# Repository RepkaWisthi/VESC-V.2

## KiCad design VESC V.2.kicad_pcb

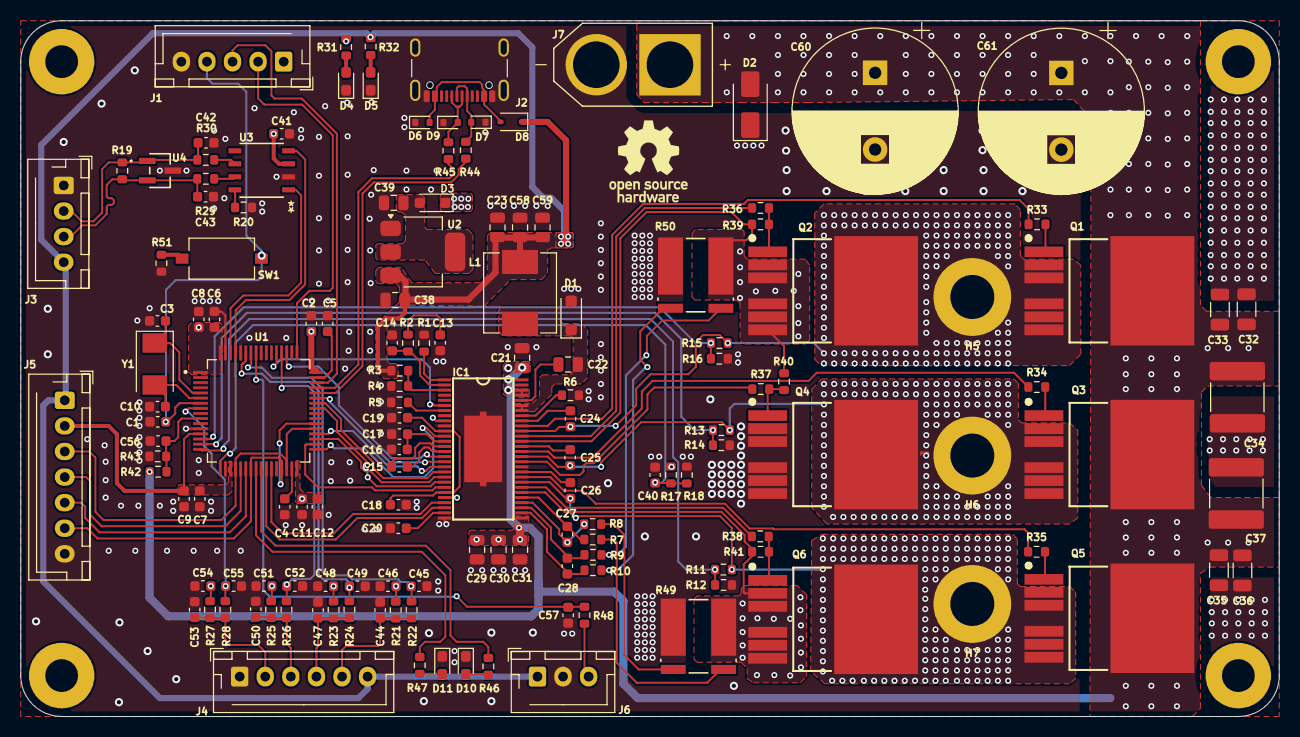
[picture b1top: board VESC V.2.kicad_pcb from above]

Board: 4 copper layers, 123.0 x 68.0 mm, 151 parts (0 on the bottom side), 102 nets.

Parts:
C1, C46, C48, C51, C54, C56, C57: 100nF; C_0603_1608Metric
C2, C4, C5, C6, C7, C8, C9, C11, C12, C16, C17, C18, C19, C20, C40, C41: 2.2uF; C_0603_1608Metric
C3, C10: 15pF; C_0603_1608Metric
C13: 6.8nF; C_0603_1608Metric
C14: 120pF; C_0603_1608Metric
C15: 22nF; C_0603_1608Metric
C21: 10uF/100V; C_0805_2012Metric
C22: 100nF; C_0805_2012Metric
C23, C38, C58, C59: 10uF; C_0805_2012Metric
C24, C25, C26: 220nF; C_0603_1608Metric
C27, C28: 2.2nF; C_0603_1608Metric
C29, C30, C31: 10uF/50V; C_0805_2012Metric
C32, C33, C35, C36: 10uF/50V; C_1206_3216Metric
C34, C37: 15uF/100V; C_2220_5750Metric
C39: 22uF; C_0805_2012Metric
C42, C43: 51pF; C_0603_1608Metric
C44, C45, C47, C49, C50, C52, C53, C55: 4.7nF; C_0603_1608Metric
C60, C61: 820uF/80V; CP_Radial_D16.0mm_P7.50mm
D1: PMEG6020; D_SOD-123F
D2: SMAJ60A; D_SMA
D3: BAT60A; D_SOD-323_HandSoldering
D4, D11: GREEN; LED_0603_1608Metric_Pad1.05x0.95mm_HandSolder
D5: RED; LED_0603_1608Metric_Pad1.05x0.95mm_HandSolder
D6, D7, D9: LESD5D5.0CT1G; D_SOD-523
D8: BAT760-7; D_SOD-323
D10: BLUE; LED_0603_1608Metric_Pad1.05x0.95mm_HandSolder
H1, H2, H3, H4: MountingHole_Pad; MountingHole_3.2mm_M3_Pad
H5, H6, H7: MountingHole_Pad; MountingHole_4.3mm_M4_ISO7380_Pad
IC1: DRV8302; TSSOP-56_3
J1: Conn_01x05_Socket; JST_XH_B5B-XH-AM_1x05_P2.50mm_Vertical
J2: USB_C_Receptacle_USB2.0_16P; USB_C_Receptacle_GCT_USB4105-xx-A_16P_TopMnt_Horizontal
J3: CAN BUS; JST_XH_B4B-XH-AM_1x04_P2.50mm_Vertical
J4: HALL SENSOR; JST_XH_B6B-XH-AM_1x06_P2.50mm_Vertical
J5: Conn_01x07_Socket; JST_XH_B7B-XH-AM_1x07_P2.50mm_Vertical
J6: Conn_01x03_Socket; JST_XH_B3B-XH-AM_1x03_P2.50mm_Vertical
J7: XT60-M; AMASS_XT60-M
L1: 22uH; L_Chilisin_BMRB00060612
Q1, Q2, Q3, Q4, Q5, Q6: IRFS7530TRL7PP; TO127P1524X483-7N
R1: 220K; R_0603_1608Metric
R2: 15K; R_0603_1608Metric
R3: 18K; R_0603_1608Metric
R4: 3.3K; R_0603_1608Metric
R5, R18, R20, R22, R24, R26, R28: 10K; R_0603_1608Metric
R6: 1M; R_0603_1608Metric
R7, R8, R9, R10: 100R; R_0603_1608Metric
R11, R13, R15, R39, R40, R41, R42: 39K; R_0603_1608Metric
R12, R14, R16: 2k2; R_0603_1608Metric
R17: NTC_10K; R_0603_1608Metric
R19: 120R; R_0603_1608Metric
R21, R23, R25, R27, R43, R48, R51: 2.2K; R_0603_1608Metric
R29, R30: 10R; R_0603_1608Metric
R31, R32, R46, R47: 1K; R_0603_1608Metric
R33, R34, R35, R36, R37, R38: 4R7; R_0603_1608Metric
R44, R45: 22R; R_0603_1608Metric
R49, R50: 1m; WSLP2726_1mOHM_VIS
SW1: SW_Push; SW_Tactile_SPST_NO_Straight_CK_PTS636Sx25SMTRLFS
U1: STM32F405RGT6; QFP50P1200X1200X160-64N
U2: AMS1117-3.3; SOT-223-3_TabPin2
U3: SN65HVD232DR; D8-L
U4: ESDCAN24-2BLY; SOT_24-2BLY_STM-M
Y1: 8MHz 10ppm; Crystal_SMD_Abracon_ABM3-2Pin_5.0x3.2mm

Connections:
+5V: C23.2, C38.1, C58.2, C59.2, D8.1 (K), J3.4, J4.6, J5.1, J6.1, L1.2, R3.1, R32.1, U2.3 (VI)
/CAN BUS/CANH: C43.2, J3.3, R19.1, R29.2, U4.2
/CAN BUS/CANL: C42.1, J3.2, R19.2, R30.2, U4.1
/CAN BUS/CAN_RX: U1.61 (PB8), U3.4 (R)
/CAN BUS/CAN_TX: U1.62 (PB9), U3.1 (D)
/HALL_FILTER/HALL1_IN: C44.1, J4.5, R21.2, R22.1
/HALL_FILTER/HALL1_OUT: C45.1, R22.2, U1.58 (PB6)
/HALL_FILTER/HALL2_IN: C47.1, J4.4, R23.2, R24.1
/HALL_FILTER/HALL2_OUT: C49.1, R24.2, U1.59 (PB7)
/HALL_FILTER/HALL3_IN: C50.1, J4.3, R25.2, R26.1
/HALL_FILTER/HALL3_OUT: C52.1, R26.2, U1.52 (PC11)
/HALL_FILTER/TEMP_IN: C53.1, J4.2, R27.2, R28.1
/HALL_FILTER/TEMP_OUT: C55.1, R28.2, U1.8 (PC0)
/MCU/ADC_TEMP: C40.1, R17.2, R18.1, U1.17 (PA3/USART2_RX)
/MCU/AN_IN: C56.1, R42.2, R43.1, U1.10 (PC2/SPI2_MISO)
/MCU/BR_S01: IC1.25 (SO1), U1.27 (PB1)
/MCU/BR_S02: IC1.26 (SO2), U1.26 (PB0)
/MCU/DC_CAL: IC1.12 (DC_CAL), U1.33 (PB12)
/MCU/EN_GATE: IC1.16 (EN_GATE), U1.51 (PC10)
/MCU/FAULT: IC1.6 (~FAULT), U1.53 (PC12)
/MCU/H1: IC1.17 (INH_A), U1.43 (PA10)
/MCU/H2: IC1.19 (INH_B), U1.42 (PA9)
/MCU/H3: IC1.21 (INH_C), U1.41 (PA8)
/MCU/L1: IC1.18 (INL_A), U1.36 (PB15)
/MCU/L2: IC1.20 (INL_B), U1.35 (PB14)
/MCU/L3: IC1.22 (INL_C), U1.34 (PB13)
/MCU/LED_GREEN: R47.1, U1.24 (PC4)
/MCU/LED_RED: R46.1, U1.25 (PC5)
/MCU/MISO_ADC_EXT2: J5.5, U1.22 (PA6/SPI1_MISO)
/MCU/RX_SCL_MOSI: J5.6, U1.23 (PA7/SPI1_MOSI), U1.29 (PB10), U1.38 (PC7)
/MCU/SCK_ADC_EXT: J5.4, U1.21 (PA5/SPI1_SCK)
/MCU/SENS1: R11.1, R12.1, U1.16 (PA2/USART2_TX)
/MCU/SENS2: R13.1, R14.1, U1.15 (PA1/USART2_RTS)
/MCU/SENS3: R15.1, R16.1, U1.14 (PA0/WKUP)
/MCU/SERVO: C57.1, R48.1, U1.57 (PB5)
/MCU/TX_SDA_NSS: J5.3, U1.20 (PA4/USART2_CK), U1.30 (PB11), U1.37 (PC6)
/MCU/USB_D+: R45.2, U1.45 (PA12)
/MCU/USB_D-: R44.2, U1.44 (PA11)
/MOSFET DRIVER/H1_VS: C24.2, H5.1, IC1.46 (SH_A), Q1.2, Q1.3, Q1.5, Q1.6, Q1.7, Q2.4, R15.2
/MOSFET DRIVER/H2_VS: C25.2, H6.1, IC1.41 (SH_B), Q3.2, Q3.3, Q3.5, Q3.6, Q3.7, Q4.4, R13.2
/MOSFET DRIVER/H3_LOW: IC1.34 (SL_C), Q6.2, Q6.3, Q6.5, Q6.6, Q6.7, R41.1, R49.1
/MOSFET DRIVER/H3_VS: C26.2, H7.1, IC1.36 (SH_C), Q5.2, Q5.3, Q5.5, Q5.6, Q5.7, Q6.4, R11.2
/MOSFET DRIVER/HI_LOW: IC1.44 (SL_A), Q2.2, Q2.3, Q2.5, Q2.6, Q2.7, R39.1, R40.1, R50.1
/MOSFET DRIVER/M_H1: IC1.47 (GH_A), R33.1
/MOSFET DRIVER/M_H2: IC1.42 (GH_B), R34.1
/MOSFET DRIVER/M_H3: IC1.37 (GH_C), R35.1
/MOSFET DRIVER/M_L1: IC1.45 (GL_A), R36.1
/MOSFET DRIVER/M_L2: IC1.40 (GL_B), R37.1
/MOSFET DRIVER/M_L3: IC1.35 (GL_C), R38.1
/MOSFET DRIVER/SH1_A: R7.2, R49.2
/MOSFET DRIVER/SH1_B: R8.2, R49.3
/MOSFET DRIVER/SH2_A: R9.2, R50.2
/MOSFET DRIVER/SH2_B: R10.2, R50.3
GND: C1.1, C2.1, C3.2, C4.2, C5.2, C6.1, C7.1, C8.1, C9.1, C10.2, C11.1, C12.1, C13.1, C14.1, C16.1, C17.1, C18.1, C19.1, C20.1, C21.2, C23.1, C29.1, C30.1, C31.1, C32.2, C33.2, C34.2, C35.2, C36.2, C37.2, C38.2, C39.2, C40.2, C41.2, C42.2, C43.1, C44.2, C45.2, C46.2, C47.2, C48.2, C49.2, C50.2, C51.2, C52.2, C53.2, C54.2, C55.2, C56.2, C57.2, C58.1, C59.1, C60.2, C61.2, D1.2 (A), D2.1 (A1), D4.1 (K), D5.1 (K), D6.1 (A1), D7.1 (A1), D9.1 (A1), D10.1 (K), D11.1 (K), IC1.8 (M_PWM), IC1.10 (GAIN), IC1.28 (AGND), IC1.39 (SL_B), IC1.57 (AGND), IC1.58 (AGND), IC1.59 (AGND), J1.5, J2.A1 (GND), J2.A12 (GND), J2.B1 (GND), J2.B12 (GND), J2.S1 (SHIELD), J3.1, J4.1, J5.7, J6.2, J7.N (NEG), Q4.2, Q4.3, Q4.5, Q4.6, Q4.7, R1.1, R4.1, R5.1, R6.2, R12.2, R14.2, R16.2, R18.2, R20.1, R43.2, R49.4, R50.4, R51.1, U1.12 (VSSA), U1.18 (VSS), U1.60 (BOOT0), U1.63 (VSS__1), U2.1 (GND), U3.2 (GND), U4.3
NRST: C1.2, J1.4, SW1.2, U1.7 (NRST)
unnamed: C13.2, R2.1
unnamed: C22.2, D1.1 (K), IC1.50 (PH), IC1.51 (PH), L1.1
unnamed: C39.1, D3.2 (A), U2.2 (VO)
unnamed: D4.2 (A), R31.2
unnamed: D5.2 (A), R32.2
unnamed: D6.2 (A2), D8.2 (A), J2.A4 (VBUS), J2.A9 (VBUS), J2.B4 (VBUS), J2.B9 (VBUS)
unnamed: D7.2 (A2), J2.A7 (D-), J2.B7 (D-), R44.1
unnamed: D9.2 (A2), J2.A6 (D+), J2.B6 (D+), R45.1
unnamed: D10.2 (A), R46.2
unnamed: D11.2 (A), R47.2
unnamed: C20.2, IC1.27 (AVDD)
unnamed: IC1.49 (BIAS), R6.1
unnamed: C24.1, IC1.48 (BST_A)
unnamed: C25.1, IC1.43 (BST_B)
unnamed: C22.1, IC1.52 (BST_BK)
unnamed: C26.1, IC1.38 (BST_C)
unnamed: C14.2, IC1.2 (COMP), R2.2
unnamed: C15.2, IC1.14 (CP1)
unnamed: C15.1, IC1.15 (CP2)
unnamed: IC1.7 (DTC), R5.2
unnamed: C18.2, C19.2, IC1.11 (OC_ADJ), IC1.23 (DVDD)
unnamed: C16.2, C17.2, IC1.13 (GVDD)
unnamed: IC1.1 (RT_CLK), R1.2
unnamed: C27.1, IC1.33 (SN1), R7.1
unnamed: C28.1, IC1.31 (SN2), R9.1
unnamed: C27.2, IC1.32 (SP1), R8.1
unnamed: C28.2, IC1.30 (SP2), R10.1
unnamed: IC1.3 (VSENSE), R3.2, R4.2
unnamed: J6.3, R48.2
unnamed: Q1.1, R33.2
unnamed: Q2.1, R36.2, R39.2
unnamed: Q3.1, R34.2
unnamed: Q4.1, R37.2, R40.2
unnamed: Q5.1, R35.2
unnamed: Q6.1, R38.2, R41.2
unnamed: R20.2, U3.8 (NC)
unnamed: R51.2, SW1.1
unnamed: C3.1, U1.5 (PH0/OSC_IN), Y1.1
unnamed: C10.1, U1.6 (PH1/OSC_OUT), Y1.2
unnamed: C4.1, U1.31 (VCAP_1)
unnamed: C5.1, U1.47 (VCAP_2)
unnamed: R29.1, U3.7 (CANH)
unnamed: R30.1, U3.6 (CANL)
SWCLK: J1.2, U1.49 (PA14/JTCK-SWCLK)
SWDIO: J1.3, U1.46 (PA13/JMS-SWDIO)
VCC: C2.2, C6.2, C7.2, C8.2, C9.2, C11.2, C12.2, C41.1, C46.1, C48.1, C51.1, C54.1, D3.1 (K), IC1.9 (M_OC), IC1.24 (REF), J1.1, J5.2, R17.1, R21.1, R23.1, R25.1, R27.1, R31.1, U1.1 (VBAT), U1.13 (VDDA), U1.19 (VDD), U1.32 (VDD__1), U1.48 (VDD__2), U1.64 (VDD__3), U3.3 (VCC)
V_SUPPLY: C21.1, C29.2, C30.2, C31.2, C32.1, C33.1, C34.1, C35.1, C36.1, C37.1, C60.1, C61.1, D2.2 (A2), IC1.29 (PVDD1), IC1.53 (PVDD2), IC1.54 (PVDD2), J7.P (POS), Q1.4, Q3.4, Q5.4, R42.1

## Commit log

2025-01-07 Initial commit for VESC V.2
2025-01-07 add open hardware logo
2025-01-11 ready for review
    1. finish routing
    2. finish silkscreen adjustment
    3. finish DRC and ERC
2025-02-11 finishing+microchecking
